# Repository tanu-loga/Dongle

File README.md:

# Dongle
My own LED Dongle       
A LED dongle which opens my github page when you press a button and flashes lights!               
I wanted a cool fun project to make and learn something new in the process. This YSWS is one of the best option I could have ever chosen, here are my snips from my pcb!                       

BOM

| Name | Cost | URL | Quantity |
| -------- | -------- | -------- | ------- |
CH552G MCU | 1.3646 | https://jlcpcb.com/partdetail/WCH_Jiangsu_Qin_Heng-CH552G/C111292 | 2 
100nF Multilayer Ceramic Capacitors MLCC - SMD/SMT| 0.276 | https://jlcpcb.com/partdetail/YAGEO-CC0603KRX7R9BB104/C14663 | 20
10K Chip Resistor - Surface Mount | 0.08 | https://jlcpcb.com/partdetail/26547-0603WAF1002T5E/C25804 | 20
330K Chip Resistor - Surface Mount | 0.0702 | https://jlcpcb.com/partdetail/23865-0603WAF3300T5E/C23138 | 26
Surface Mount,Vertical Without Bracket SMD,4x3mm Tactile Switches ROHS X2| 0.3792 | https://jlcpcb.com/partdetail/XUNPU-TS_1088R02026/C455280 | 6
2mm x 1.25mm square LED Red | 0.299 | https://jlcpcb.com/partdetail/Hubei_KENTOElec-KT0805R/C2295 | 26
USB_A | 0.161 | https://jlcpcb.com/partdetail/SOFNG-USB05/C112454 | 2
Total cost: $120.43

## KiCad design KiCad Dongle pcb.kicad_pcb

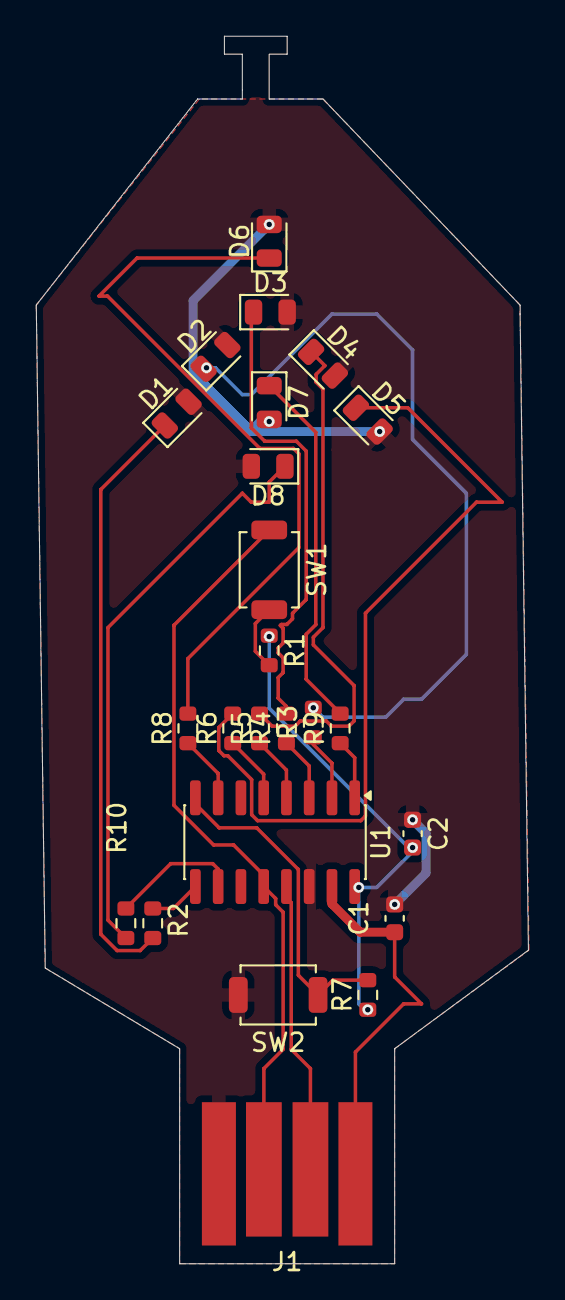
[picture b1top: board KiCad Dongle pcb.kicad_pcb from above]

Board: 2 copper layers, 27.5 x 68.5 mm, 24 parts (0 on the bottom side), 23 nets.

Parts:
C1, C2: 100nF; C_0603_1608Metric
D1, D2, D3, D4, D5, D6, D7, D8: LED; LED_0805_2012Metric
J1: USB_A; USB-A
R1, R7: 10K; R_0603_1608Metric
R2, R3, R4, R5, R6, R8, R9, R10: 330R; R_0603_1608Metric
SW1, SW2: SW_Push; SW_SPST_TS-1088-xR020
U1: CH552G; SOIC-16_3.9x9.9mm_P1.27mm

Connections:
+3V3: C2.2, R1.1, R7.1, U1.16 (3V3)
/D+: J1.3 (D+), SW1.1, U1.12 (P3.6)
/D-: J1.2 (D-), U1.13 (P3.7)
/P1.1: R2.1, U1.9 (P1.1)
/P1.4: R3.1, U1.2 (P1.4)
/P1.5: R4.1, U1.3 (P1.5)
/P1.6: R5.1, U1.4 (P1.6)
/P1.7: R6.1, U1.5 (P1.7)
/P3.0: R7.2, SW2.1, U1.8 (P3.0)
/P3.1: R8.1, U1.7 (P3.1)
/P3.2: R9.1, U1.1 (P3.2)
/P3.3: R10.1, U1.10 (P3.3)
GND: C1.2, C2.1, D1.2 (A), D2.2 (A), D3.2 (A), D4.2 (A), D5.2 (A), D6.2 (A), D7.2 (A), D8.2 (A), J1.4 (GND), SW2.2, U1.14 (GND)
unnamed: D1.1 (K), R2.2
unnamed: D2.1 (K), R3.2
unnamed: D3.1 (K), R4.2
unnamed: D4.1 (K), R5.2
unnamed: D5.1 (K), R6.2
unnamed: D6.1 (K), R8.2
unnamed: D7.1 (K), R9.2
unnamed: D8.1 (K), R10.2
unnamed: R1.2, SW1.2
VBUS: C1.1, J1.1 (VBUS), U1.15 (VCC)
